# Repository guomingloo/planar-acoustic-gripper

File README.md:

# planar-acoustic-gripper
Source code ,simulation logs and design files for a 66-channel flat-panel ultrasonic phased array acoustic gripper based on Cyclone IV FPGA integrated with a FLEXIV Rizon 4s 7-DOF robot. EE FYP 2025/2026, Universiti Sains Malaysia (USM).

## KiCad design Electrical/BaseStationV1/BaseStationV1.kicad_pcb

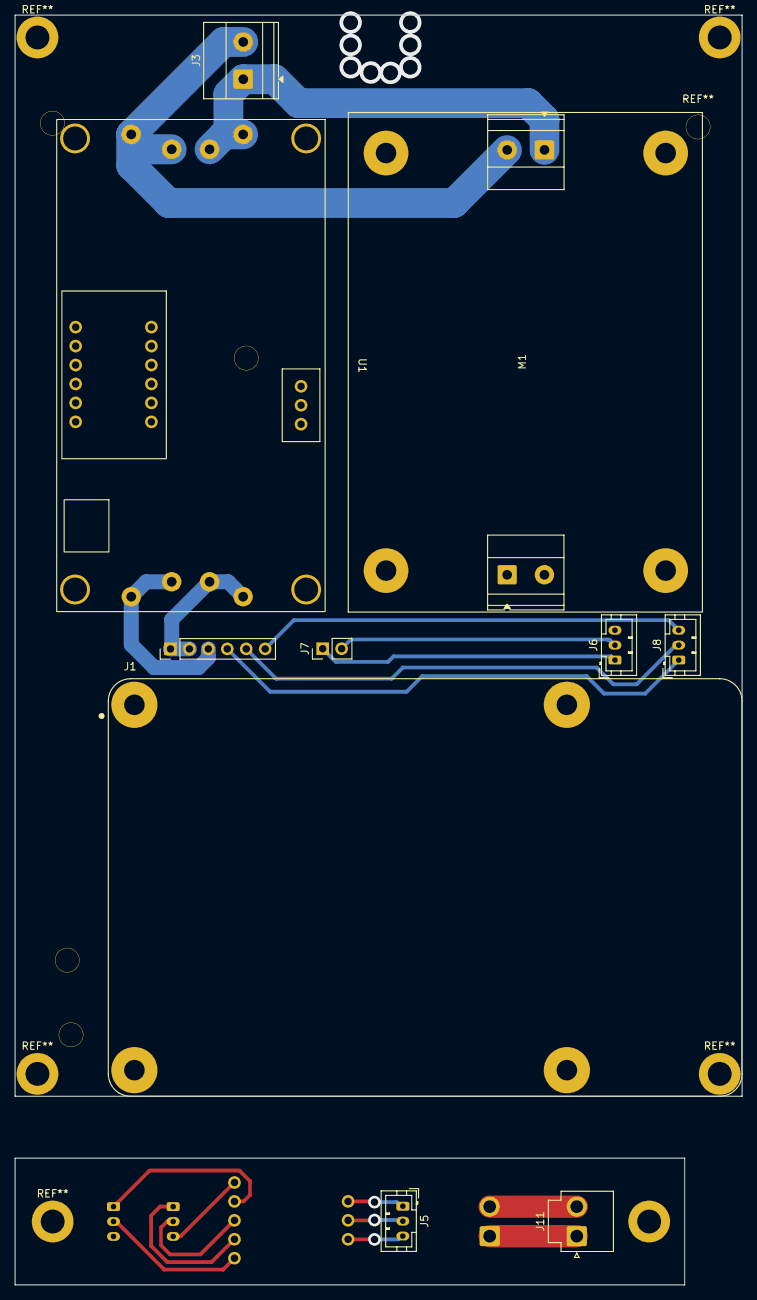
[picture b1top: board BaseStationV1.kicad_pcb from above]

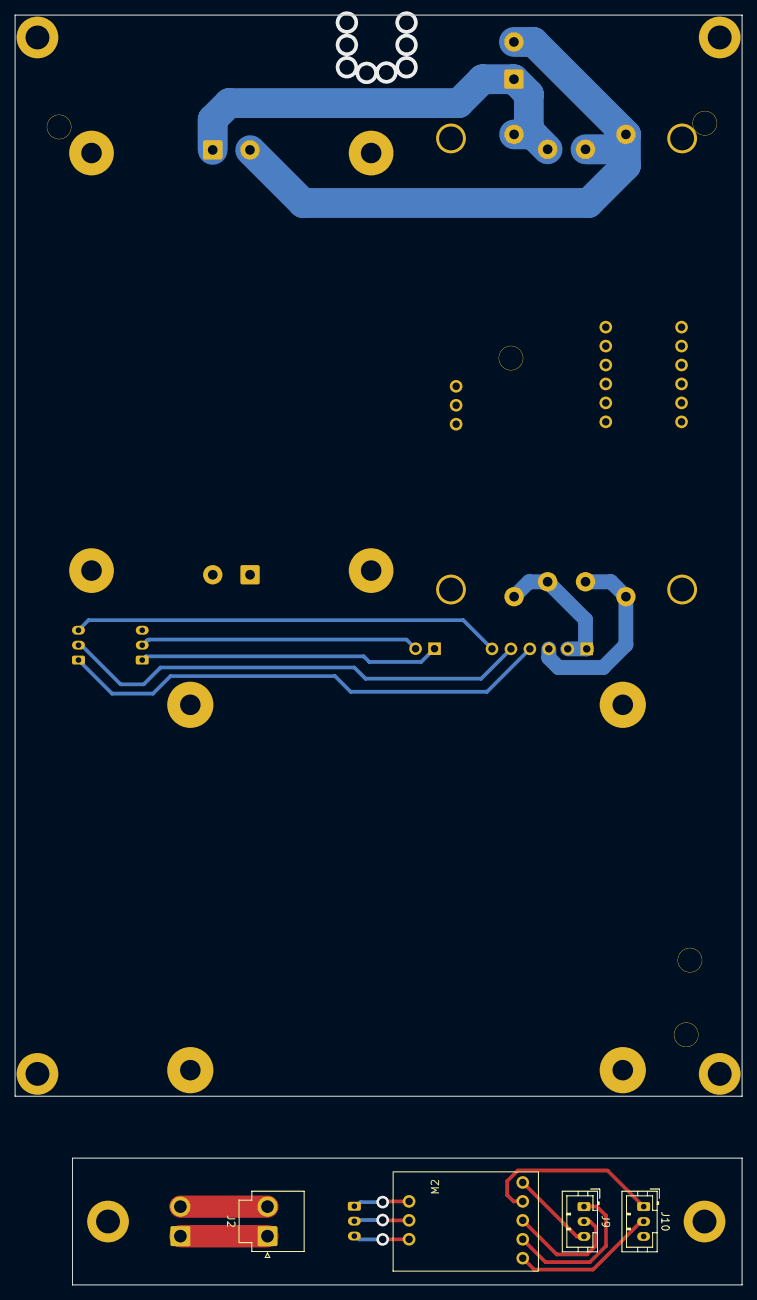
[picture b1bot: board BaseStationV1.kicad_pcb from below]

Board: 2 copper layers, 97.5 x 170.3 mm, 14 parts (4 on the bottom side), 13 nets.

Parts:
J1: Raspberry_Pi_4; MODULE_RASPBERRY_PI_4B_4GB
J2, J11: Conn_01x02_Pin; JST_VH_B2P-VH-B_1x02_P3.96mm_Vertical
J3: Screw_Terminal_01x02; TerminalBlock_Phoenix_MKDS-1,5-2_1x02_P5.00mm_Horizontal
J4: Conn_01x06_Pin; PinHeader_1x06_P2.54mm_Vertical
J5, J6, J8, J9, J10: Conn_01x03_Pin; JST_PH_B3B-PH-K_1x03_P2.00mm_Vertical
J7: Conn_01x02_Pin; PinHeader_1x02_P2.54mm_Vertical
M1: Boost_Converter_Module
M2: MAX3485_Module
U1: Module_LM2596_Display

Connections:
+3V3: J6.1, J7.1, J10.1, M2.7 (VCC)
+5V: J4.1, J4.2, U1.3 (OUT+)
GND: J4.3, J6.2, J7.2, J10.2, M2.4 (GND), U1.4 (OUT-)
unnamed: J4.4, J8.1, J9.1, M2.5 (TX)
unnamed: J4.5, J8.2, J9.2, M2.6 (RX)
unnamed: J4.6, J8.3, J9.3, M2.8 (EN)
unnamed: J3.1, M1.2 (IN+), U1.1 (IN+)
unnamed: J3.2, M1.1 (IN-), U1.2 (IN-)
unnamed: J5.1, M2.1 (B)
unnamed: J5.2, M2.2 (A)
unnamed: J5.3, M2.3 (GND)
unnamed: J2.1, J11.1
unnamed: J2.2, J11.2, M1.3 (OUT-)

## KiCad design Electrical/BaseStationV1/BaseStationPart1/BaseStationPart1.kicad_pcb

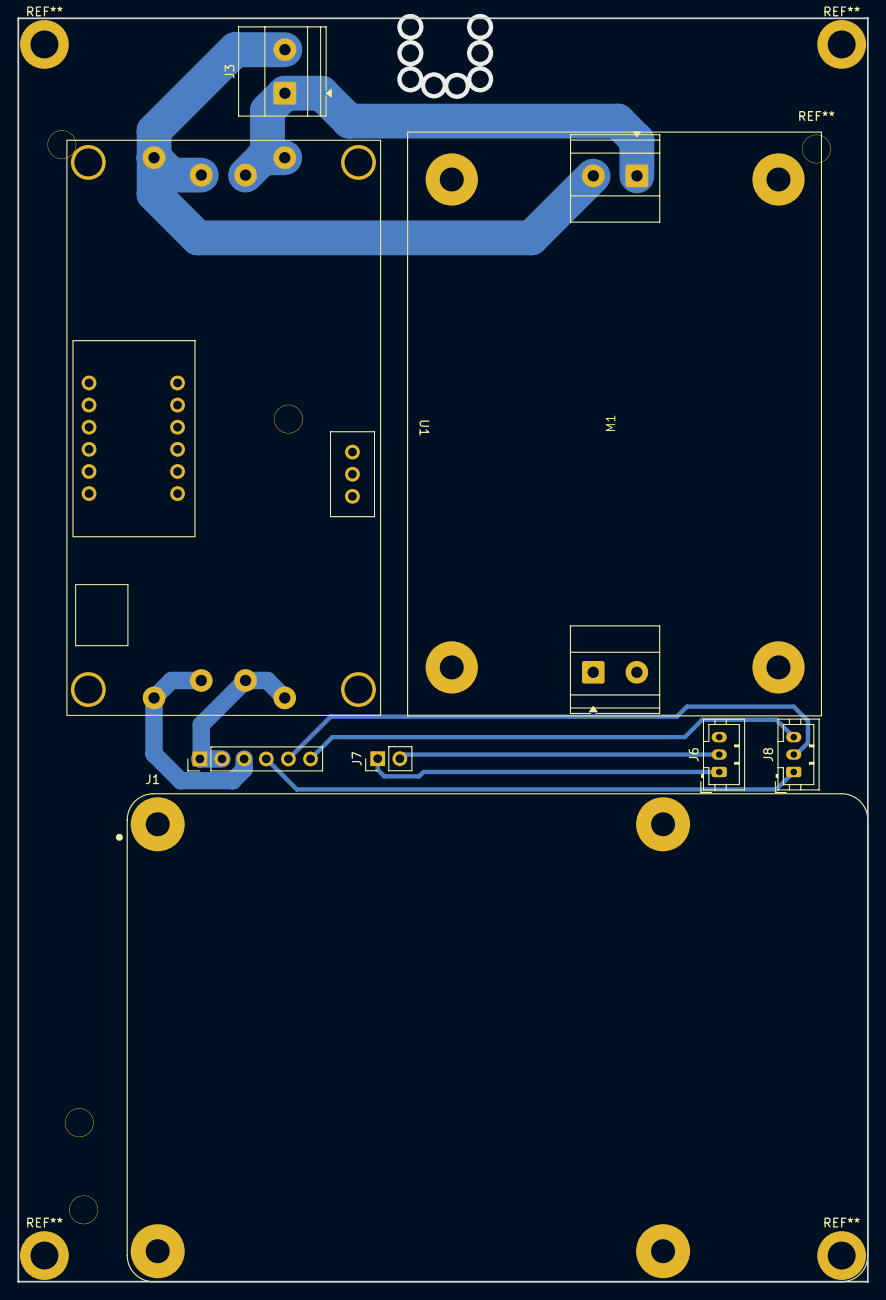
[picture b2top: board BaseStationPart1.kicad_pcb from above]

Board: 2 copper layers, 97.5 x 145.0 mm, 8 parts (0 on the bottom side), 8 nets.

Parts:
J1: Raspberry_Pi_4; MODULE_RASPBERRY_PI_4B_4GB
J3: Screw_Terminal_01x02; TerminalBlock_Phoenix_MKDS-1,5-2_1x02_P5.00mm_Horizontal
J4: Conn_01x06_Pin; PinHeader_1x06_P2.54mm_Vertical
J6, J8: Conn_01x03_Pin; JST_PH_B3B-PH-K_1x03_P2.00mm_Vertical
J7: Conn_01x02_Pin; PinHeader_1x02_P2.54mm_Vertical
M1: Boost_Converter_Module
U1: Module_LM2596_Display

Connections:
+3V3: J6.1, J7.1
+5V: J4.1, J4.2, U1.3 (OUT+)
GND: J4.3, J6.2, J7.2, U1.4 (OUT-)
unnamed: J4.4, J8.1
unnamed: J4.5, J8.2
unnamed: J4.6, J8.3
unnamed: J3.1, M1.2 (IN+), U1.1 (IN+)
unnamed: J3.2, M1.1 (IN-), U1.2 (IN-)

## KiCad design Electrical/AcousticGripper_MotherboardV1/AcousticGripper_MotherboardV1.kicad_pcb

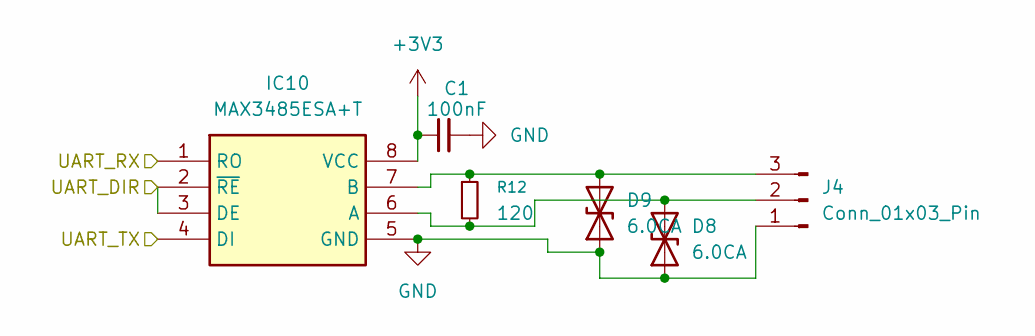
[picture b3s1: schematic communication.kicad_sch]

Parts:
C1: 100nF; C_0402_1005Metric
D8, D9: 6.0CA; D_SMA
IC10: MAX3485ESA+T; SOIC127P600X175-8N; Mouser Part Number 700-MAX3485ESAT
J4: Conn_01x03_Pin; JST_PH_B3B-PH-K_1x03_P2.00mm_Vertical
R12: 120; R_0402_1005Metric

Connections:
+3V3: C1.1, IC10.8 (VCC); also elsewhere on the board
/FPGA_Core/FPGA_TX3: IC10.4 (DI); also elsewhere on the board
/FPGA_Core/FPGA_TX4: IC10.1 (RO); also elsewhere on the board
/FPGA_Core/FPGA_TX80: IC10.2 (~RE), IC10.3 (DE); also elsewhere on the board
GND: C1.2, D8.1 (A1), D9.1 (A1), IC10.5 (GND), J4.1; also elsewhere on the board
unnamed: D8.2 (A2), IC10.6 (A), J4.2, R12.2
unnamed: D9.2 (A2), IC10.7 (B), J4.3, R12.1

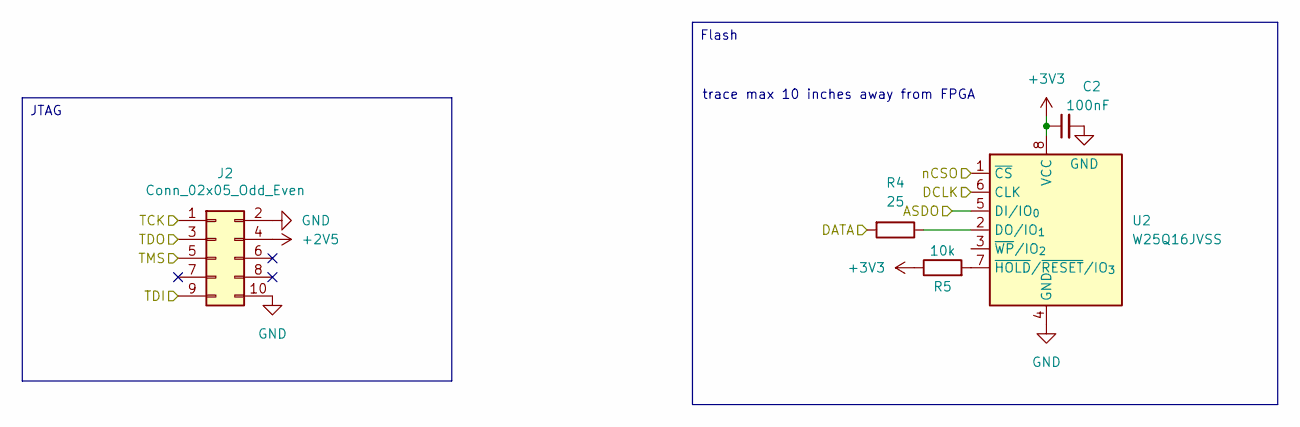
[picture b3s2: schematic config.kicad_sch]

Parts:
C2: 100nF; C_0402_1005Metric
J2: Conn_02x05_Odd_Even; IDC-Header_2x05_P2.54mm_Vertical
R4: 25; R_0402_1005Metric
R5: 10k; R_0402_1005Metric
U2: W25Q16JVSS; SOIC-8_5.3x5.3mm_P1.27mm

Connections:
+2V5: J2.4; also elsewhere on the board
+3V3: C2.1, R5.1, U2.8 (VCC); also elsewhere on the board
/Configuration/ASDO: U2.5 (DI/IO_{0}); also elsewhere on the board
/Configuration/DATA: R4.2; also elsewhere on the board
/Configuration/DCLK: U2.6 (CLK); also elsewhere on the board
/Configuration/TCK: J2.1; also elsewhere on the board
/Configuration/TDI: J2.9; also elsewhere on the board
/Configuration/TDO: J2.3; also elsewhere on the board
/Configuration/TMS: J2.5; also elsewhere on the board
/Configuration/nCSO: U2.1 (~CS); also elsewhere on the board
GND: C2.2, J2.2, J2.10, U2.4 (GND); also elsewhere on the board
unnamed: R4.1, U2.2 (DO/IO_{1})
unnamed: R5.2, U2.7 (~HOLD/~RESET/IO_{3})

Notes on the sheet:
trace max 10 inches away from FPGA
Flash
JTAG

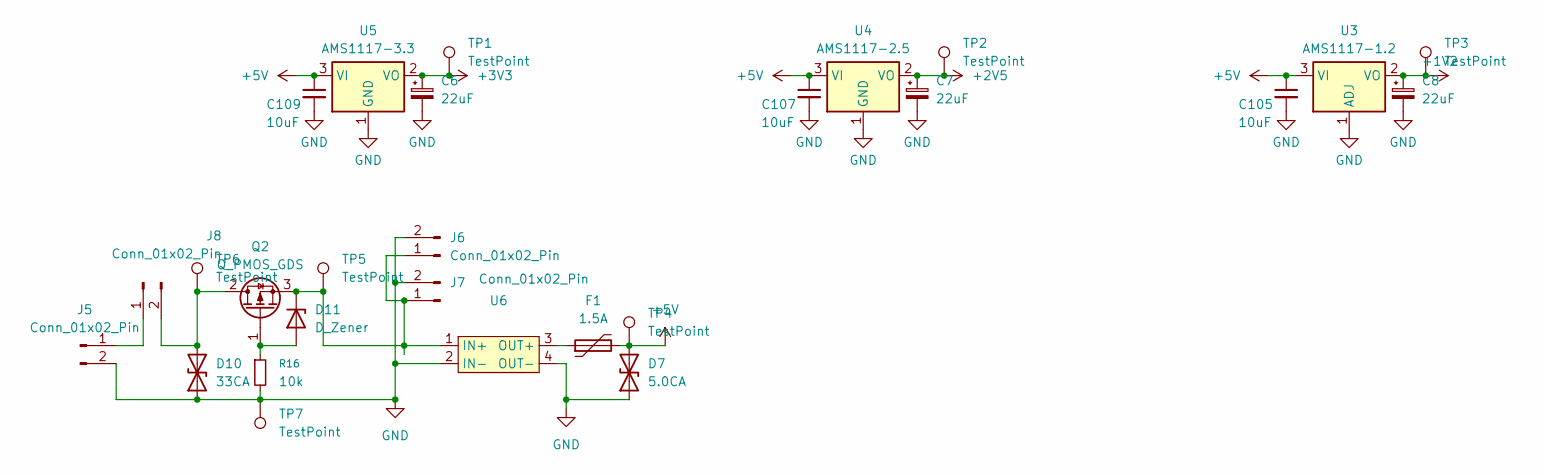
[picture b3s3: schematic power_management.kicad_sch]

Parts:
C6, C7, C8: 22uF; CP_EIA-3216-18_Kemet-A
C105, C107, C109: 10uF; C_0402_1005Metric
D7: 5.0CA; D_SMA
D10: 33CA; D_SMC
D11: D_Zener; D_SOD-323F
F1: 1.5A; Fuse_1206_3216Metric
J5, J6, J7, J8: Conn_01x02_Pin; JST_VH_B2P-VH-B_1x02_P3.96mm_Vertical
Q2: Q_PMOS_GDS; TO-252-2
R16: 10k; R_0402_1005Metric
TP1, TP2, TP3, TP4, TP5, TP6, TP7: TestPoint; TestPoint_Pad_D1.0mm
U3: AMS1117-1.2; SOT-223-3_TabPin2
U4: AMS1117-2.5; SOT-223-3_TabPin2
U5: AMS1117-3.3; SOT-223-3_TabPin2
U6: 4050S_Buck_Converter_Module

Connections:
+1V2: C8.1, TP3.1, U3.2 (VO); also elsewhere on the board
+2V5: C7.1, TP2.1, U4.2 (VO); also elsewhere on the board
+3V3: C6.1, TP1.1, U5.2 (VO); also elsewhere on the board
+5V: C105.1, C107.1, C109.1, D7.2 (A2), F1.2, TP4.1, U3.3 (VI), U4.3 (VI), U5.3 (VI); also elsewhere on the board
GND: C6.2, C7.2, C8.2, C105.2, C107.2, C109.2, D7.1 (A1), D10.1 (A1), J5.2, J6.2, J7.2, R16.2, TP7.1, U3.1 (ADJ), U4.1 (GND), U5.1 (GND), U6.2 (IN-), U6.4 (OUT-); also elsewhere on the board
unnamed: D10.2 (A2), J8.2, Q2.2 (D), TP6.1
unnamed: D11.2 (A), Q2.1 (G), R16.1
unnamed: D11.1 (K), J6.1, J7.1, Q2.3 (S), TP5.1, U6.1 (IN+)
unnamed: J5.1, J8.1
unnamed: F1.1, U6.3 (OUT+)

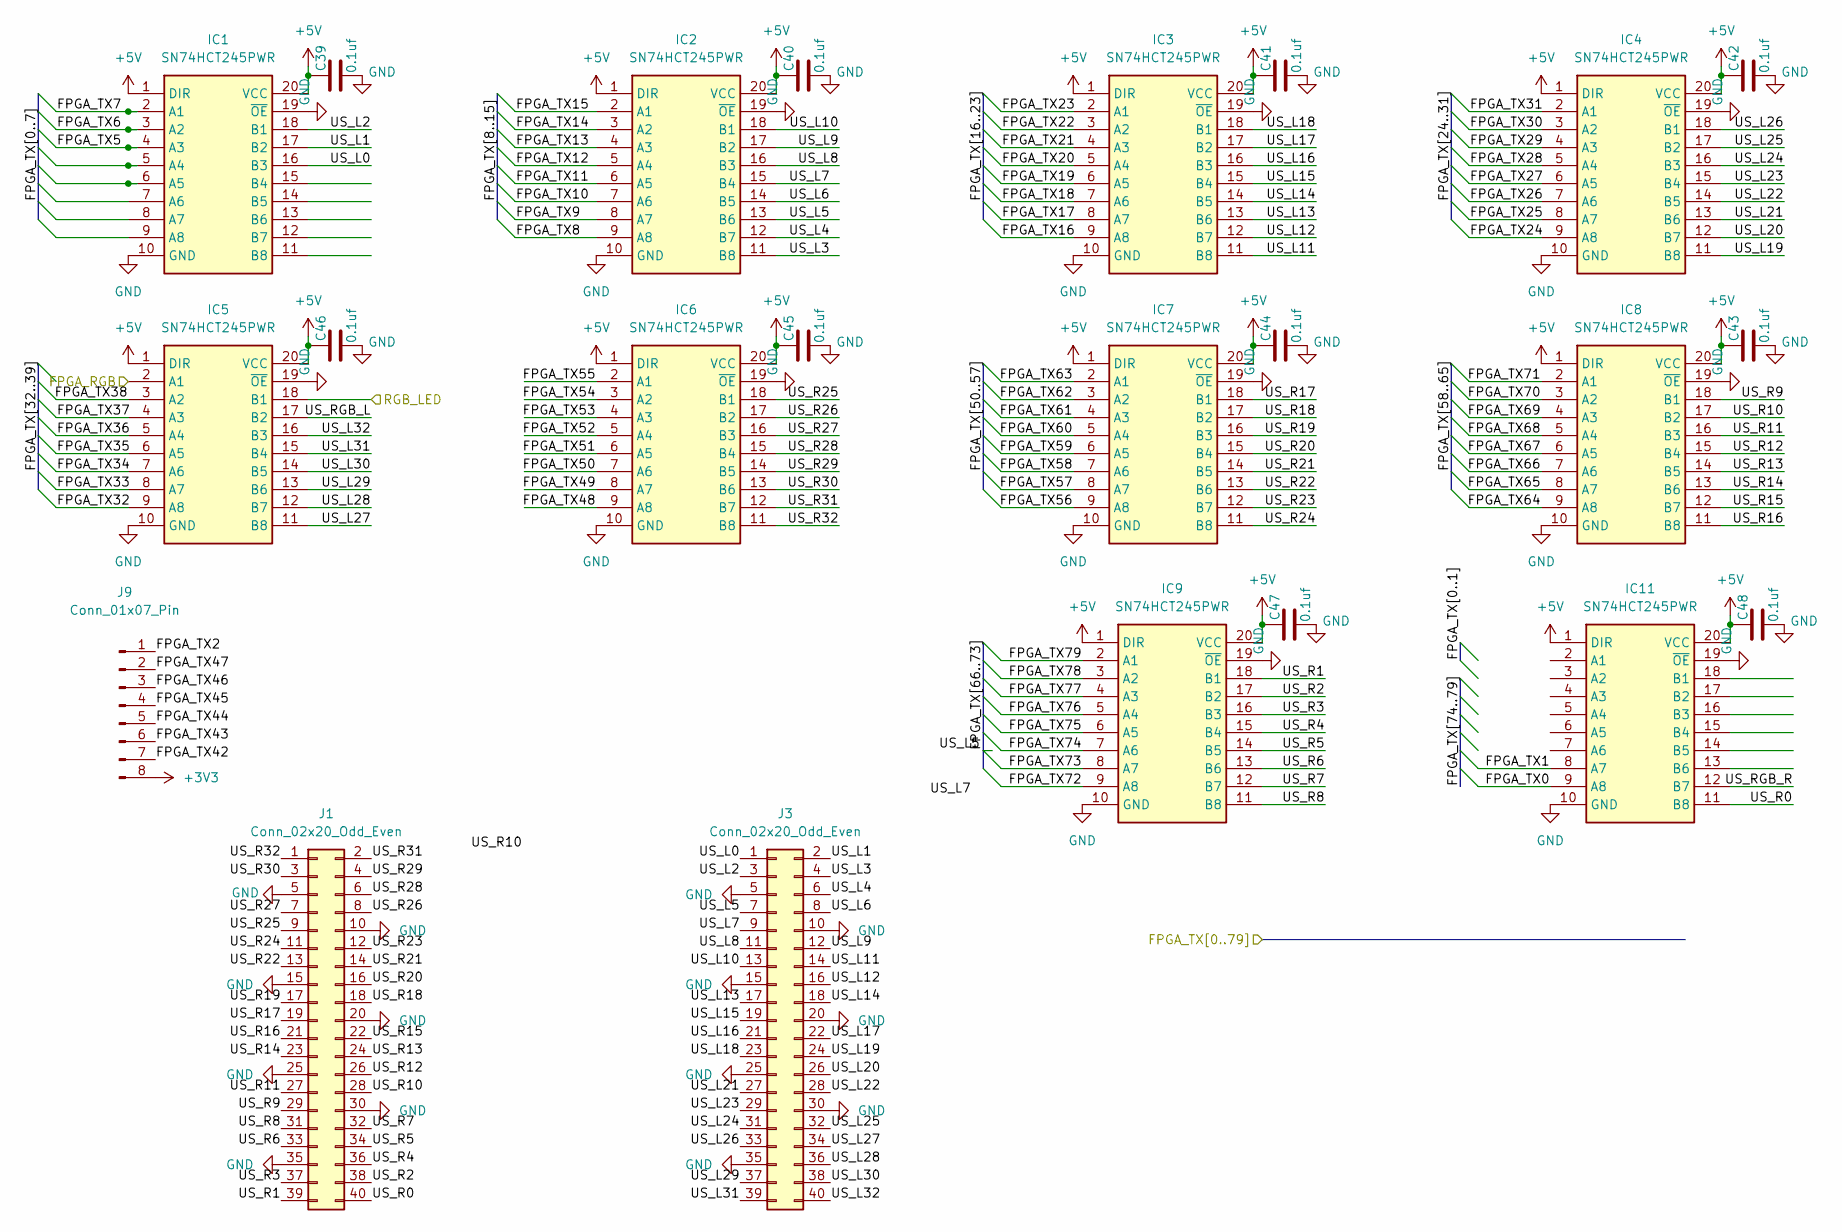
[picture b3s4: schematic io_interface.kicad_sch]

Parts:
C39, C40, C41, C42, C43, C44, C45, C46, C47, C48: 0.1uf; C_0402_1005Metric
IC1, IC2, IC3, IC4, IC5, IC6, IC7, IC8, IC9, IC11: SN74HCT245PWR; SOP65P640X120-20N; Mouser Part Number 595-SN74HCT245PWR
J1, J3: Conn_02x20_Odd_Even; IDC-Header_2x20_P2.54mm_Vertical
J9: Conn_01x07_Pin; PinHeader_2x04_P2.54mm_Vertical

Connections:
+3V3: J9.8; also elsewhere on the board
+5V: C39.1, C40.1, C41.1, C42.1, C43.1, C44.1, C45.1, C46.1, C47.1, C48.1, IC1.1 (DIR), IC1.20 (VCC), IC2.1 (DIR), IC2.20 (VCC), IC3.1 (DIR), IC3.20 (VCC), IC4.1 (DIR), IC4.20 (VCC), IC5.1 (DIR), IC5.20 (VCC), IC6.1 (DIR), IC6.20 (VCC), IC7.1 (DIR), IC7.20 (VCC), IC8.1 (DIR), IC8.20 (VCC), IC9.1 (DIR), IC9.20 (VCC), IC11.1 (DIR), IC11.20 (VCC); also elsewhere on the board
/FPGA_Core/FPGA_TX0: IC11.9 (A8); also elsewhere on the board
/FPGA_Core/FPGA_TX1: IC11.8 (A7); also elsewhere on the board
/FPGA_Core/FPGA_TX2: J9.1; also elsewhere on the board
/FPGA_Core/FPGA_TX5: IC1.4 (A3); also elsewhere on the board
/FPGA_Core/FPGA_TX6: IC1.3 (A2); also elsewhere on the board
/FPGA_Core/FPGA_TX7: IC1.2 (A1); also elsewhere on the board
/FPGA_Core/FPGA_TX8: IC2.9 (A8); also elsewhere on the board
/FPGA_Core/FPGA_TX9: IC2.8 (A7); also elsewhere on the board
/FPGA_Core/FPGA_TX10: IC2.7 (A6); also elsewhere on the board
/FPGA_Core/FPGA_TX11: IC2.6 (A5); also elsewhere on the board
/FPGA_Core/FPGA_TX12: IC2.5 (A4); also elsewhere on the board
/FPGA_Core/FPGA_TX13: IC2.4 (A3); also elsewhere on the board
/FPGA_Core/FPGA_TX14: IC2.3 (A2); also elsewhere on the board
/FPGA_Core/FPGA_TX15: IC2.2 (A1); also elsewhere on the board
/FPGA_Core/FPGA_TX16: IC3.9 (A8); also elsewhere on the board
/FPGA_Core/FPGA_TX17: IC3.8 (A7); also elsewhere on the board
/FPGA_Core/FPGA_TX18: IC3.7 (A6); also elsewhere on the board
/FPGA_Core/FPGA_TX19: IC3.6 (A5); also elsewhere on the board
/FPGA_Core/FPGA_TX20: IC3.5 (A4); also elsewhere on the board
/FPGA_Core/FPGA_TX21: IC3.4 (A3); also elsewhere on the board
/FPGA_Core/FPGA_TX22: IC3.3 (A2); also elsewhere on the board
/FPGA_Core/FPGA_TX23: IC3.2 (A1); also elsewhere on the board
/FPGA_Core/FPGA_TX24: IC4.9 (A8); also elsewhere on the board
/FPGA_Core/FPGA_TX25: IC4.8 (A7); also elsewhere on the board
/FPGA_Core/FPGA_TX26: IC4.7 (A6); also elsewhere on the board
/FPGA_Core/FPGA_TX27: IC4.6 (A5); also elsewhere on the board
/FPGA_Core/FPGA_TX28: IC4.5 (A4); also elsewhere on the board
/FPGA_Core/FPGA_TX29: IC4.4 (A3); also elsewhere on the board
/FPGA_Core/FPGA_TX30: IC4.3 (A2); also elsewhere on the board
/FPGA_Core/FPGA_TX31: IC4.2 (A1); also elsewhere on the board
/FPGA_Core/FPGA_TX32: IC5.9 (A8); also elsewhere on the board
/FPGA_Core/FPGA_TX33: IC5.8 (A7); also elsewhere on the board
/FPGA_Core/FPGA_TX34: IC5.7 (A6); also elsewhere on the board
/FPGA_Core/FPGA_TX35: IC5.6 (A5); also elsewhere on the board
/FPGA_Core/FPGA_TX36: IC5.5 (A4); also elsewhere on the board
/FPGA_Core/FPGA_TX37: IC5.4 (A3); also elsewhere on the board
/FPGA_Core/FPGA_TX38: IC5.3 (A2); also elsewhere on the board
/FPGA_Core/FPGA_TX39: IC5.2 (A1); also elsewhere on the board
/FPGA_Core/FPGA_TX42: J9.7; also elsewhere on the board
/FPGA_Core/FPGA_TX43: J9.6; also elsewhere on the board
/FPGA_Core/FPGA_TX44: J9.5; also elsewhere on the board
/FPGA_Core/FPGA_TX45: J9.4; also elsewhere on the board
/FPGA_Core/FPGA_TX46: J9.3; also elsewhere on the board
/FPGA_Core/FPGA_TX47: J9.2; also elsewhere on the board
/FPGA_Core/FPGA_TX48: IC6.9 (A8); also elsewhere on the board
/FPGA_Core/FPGA_TX49: IC6.8 (A7); also elsewhere on the board
/FPGA_Core/FPGA_TX50: IC6.7 (A6); also elsewhere on the board
/FPGA_Core/FPGA_TX51: IC6.6 (A5); also elsewhere on the board
/FPGA_Core/FPGA_TX52: IC6.5 (A4); also elsewhere on the board
/FPGA_Core/FPGA_TX53: IC6.4 (A3); also elsewhere on the board
/FPGA_Core/FPGA_TX54: IC6.3 (A2); also elsewhere on the board
/FPGA_Core/FPGA_TX55: IC6.2 (A1); also elsewhere on the board
/FPGA_Core/FPGA_TX56: IC7.9 (A8); also elsewhere on the board
/FPGA_Core/FPGA_TX57: IC7.8 (A7); also elsewhere on the board
/FPGA_Core/FPGA_TX58: IC7.7 (A6); also elsewhere on the board
/FPGA_Core/FPGA_TX59: IC7.6 (A5); also elsewhere on the board
/FPGA_Core/FPGA_TX60: IC7.5 (A4); also elsewhere on the board
/FPGA_Core/FPGA_TX61: IC7.4 (A3); also elsewhere on the board
/FPGA_Core/FPGA_TX62: IC7.3 (A2); also elsewhere on the board
/FPGA_Core/FPGA_TX63: IC7.2 (A1); also elsewhere on the board
/FPGA_Core/FPGA_TX64: IC8.9 (A8); also elsewhere on the board
/FPGA_Core/FPGA_TX65: IC8.8 (A7); also elsewhere on the board
/FPGA_Core/FPGA_TX66: IC8.7 (A6); also elsewhere on the board
/FPGA_Core/FPGA_TX67: IC8.6 (A5); also elsewhere on the board
/FPGA_Core/FPGA_TX68: IC8.5 (A4); also elsewhere on the board
/FPGA_Core/FPGA_TX69: IC8.4 (A3); also elsewhere on the board
/FPGA_Core/FPGA_TX70: IC8.3 (A2); also elsewhere on the board
/FPGA_Core/FPGA_TX71: IC8.2 (A1); also elsewhere on the board
/FPGA_Core/FPGA_TX72: IC9.9 (A8); also elsewhere on the board
/FPGA_Core/FPGA_TX73: IC9.8 (A7); also elsewhere on the board
/FPGA_Core/FPGA_TX74: IC9.7 (A6); also elsewhere on the board
/FPGA_Core/FPGA_TX75: IC9.6 (A5); also elsewhere on the board
/FPGA_Core/FPGA_TX76: IC9.5 (A4); also elsewhere on the board
/FPGA_Core/FPGA_TX77: IC9.4 (A3); also elsewhere on the board
/FPGA_Core/FPGA_TX78: IC9.3 (A2); also elsewhere on the board
/FPGA_Core/FPGA_TX79: IC9.2 (A1); also elsewhere on the board
/IO_Interface/RGB_LED: IC5.18 (B1); also elsewhere on the board
/IO_Interface/US_L0: IC1.16 (B3), J3.1
/IO_Interface/US_L1: IC1.17 (B2), J3.2
/IO_Interface/US_L2: IC1.18 (B1), J3.3
/IO_Interface/US_L3: IC2.11 (B8), J3.4
/IO_Interface/US_L4: IC2.12 (B7), J3.6
/IO_Interface/US_L5: IC2.13 (B6), J3.7
/IO_Interface/US_L6: IC2.14 (B5), J3.8
/IO_Interface/US_L7: IC2.15 (B4), J3.9
/IO_Interface/US_L8: IC2.16 (B3), J3.11
/IO_Interface/US_L9: IC2.17 (B2), J3.12
/IO_Interface/US_L10: IC2.18 (B1), J3.13
/IO_Interface/US_L11: IC3.11 (B8), J3.14
/IO_Interface/US_L12: IC3.12 (B7), J3.16
/IO_Interface/US_L13: IC3.13 (B6), J3.17
/IO_Interface/US_L14: IC3.14 (B5), J3.18
/IO_Interface/US_L15: IC3.15 (B4), J3.19
/IO_Interface/US_L16: IC3.16 (B3), J3.21
/IO_Interface/US_L17: IC3.17 (B2), J3.22
/IO_Interface/US_L18: IC3.18 (B1), J3.23
/IO_Interface/US_L19: IC4.11 (B8), J3.24
/IO_Interface/US_L20: IC4.12 (B7), J3.26
/IO_Interface/US_L21: IC4.13 (B6), J3.27
/IO_Interface/US_L22: IC4.14 (B5), J3.28
/IO_Interface/US_L23: IC4.15 (B4), J3.29
/IO_Interface/US_L24: IC4.16 (B3), J3.31
/IO_Interface/US_L25: IC4.17 (B2), J3.32
/IO_Interface/US_L26: IC4.18 (B1), J3.33
/IO_Interface/US_L27: IC5.11 (B8), J3.34
/IO_Interface/US_L28: IC5.12 (B7), J3.36
/IO_Interface/US_L29: IC5.13 (B6), J3.37
/IO_Interface/US_L30: IC5.14 (B5), J3.38
/IO_Interface/US_L31: IC5.15 (B4), J3.39
/IO_Interface/US_L32: IC5.16 (B3), J3.40
/IO_Interface/US_R0: IC11.11 (B8), J1.40
/IO_Interface/US_R1: IC9.18 (B1), J1.39
/IO_Interface/US_R2: IC9.17 (B2), J1.38
/IO_Interface/US_R3: IC9.16 (B3), J1.37
/IO_Interface/US_R4: IC9.15 (B4), J1.36
/IO_Interface/US_R5: IC9.14 (B5), J1.34
/IO_Interface/US_R6: IC9.13 (B6), J1.33
/IO_Interface/US_R7: IC9.12 (B7), J1.32
/IO_Interface/US_R8: IC9.11 (B8), J1.31
/IO_Interface/US_R9: IC8.18 (B1), J1.29
/IO_Interface/US_R10: IC8.17 (B2), J1.28
/IO_Interface/US_R11: IC8.16 (B3), J1.27
/IO_Interface/US_R12: IC8.15 (B4), J1.26
/IO_Interface/US_R13: IC8.14 (B5), J1.24
/IO_Interface/US_R14: IC8.13 (B6), J1.23
/IO_Interface/US_R15: IC8.12 (B7), J1.22
/IO_Interface/US_R16: IC8.11 (B8), J1.21
/IO_Interface/US_R17: IC7.18 (B1), J1.19
/IO_Interface/US_R18: IC7.17 (B2), J1.18
/IO_Interface/US_R19: IC7.16 (B3), J1.17
/IO_Interface/US_R20: IC7.15 (B4), J1.16
/IO_Interface/US_R21: IC7.14 (B5), J1.14
/IO_Interface/US_R22: IC7.13 (B6), J1.13
/IO_Interface/US_R23: IC7.12 (B7), J1.12
/IO_Interface/US_R24: IC7.11 (B8), J1.11
/IO_Interface/US_R25: IC6.18 (B1), J1.9
/IO_Interface/US_R26: IC6.17 (B2), J1.8
/IO_Interface/US_R27: IC6.16 (B3), J1.7
/IO_Interface/US_R28: IC6.15 (B4), J1.6
/IO_Interface/US_R29: IC6.14 (B5), J1.4
/IO_Interface/US_R30: IC6.13 (B6), J1.3
/IO_Interface/US_R31: IC6.12 (B7), J1.2
/IO_Interface/US_R32: IC6.11 (B8), J1.1
/IO_Interface/US_RGB_L: IC5.17 (B2)
/IO_Interface/US_RGB_R: IC11.12 (B7)
GND: C39.2, C40.2, C41.2, C42.2, C43.2, C44.2, C45.2, C46.2, C47.2, C48.2, IC1.10 (GND), IC1.19 (~OE), IC2.10 (GND), IC2.19 (~OE), IC3.10 (GND), IC3.19 (~OE), IC4.10 (GND), IC4.19 (~OE), IC5.10 (GND), IC5.19 (~OE), IC6.10 (GND), IC6.19 (~OE), IC7.10 (GND), IC7.19 (~OE), IC8.10 (GND), IC8.19 (~OE), IC9.10 (GND), IC9.19 (~OE), IC11.10 (GND), IC11.19 (~OE), J1.5, J1.10, J1.15, J1.20, J1.25, J1.30, J1.35, J3.5, J3.10, J3.15, J3.20, J3.25, J3.30, J3.35; also elsewhere on the board
